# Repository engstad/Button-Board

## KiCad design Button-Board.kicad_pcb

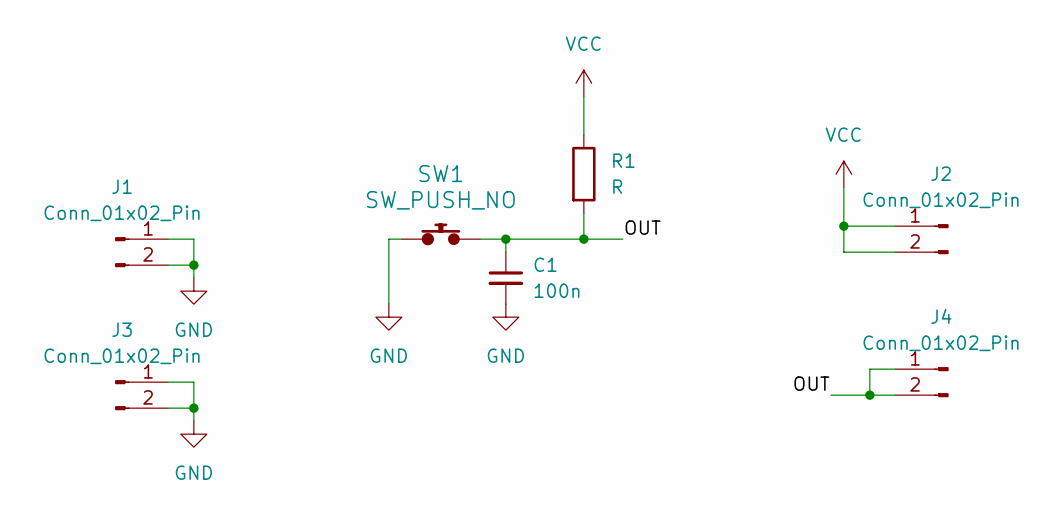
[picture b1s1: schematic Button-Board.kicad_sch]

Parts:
C1: 100n; C_0603_1608Metric_Pad1.08x0.95mm_HandSolder
J1, J2, J3, J4: Conn_01x02_Pin; PinHeader_1x02_P2.54mm_Vertical
R1: R; R_0603_1608Metric_Pad0.98x0.95mm_HandSolder
SW1: SW_PUSH_NO; TACTILE_SWITCH-TE-FSM4JSMAATR

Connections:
/OUT: C1.1, J4.1, J4.2, R1.2, SW1.2
GND: C1.2, J1.1, J1.2, J3.1, J3.2, SW1.1
VCC: J2.1, J2.2, R1.1

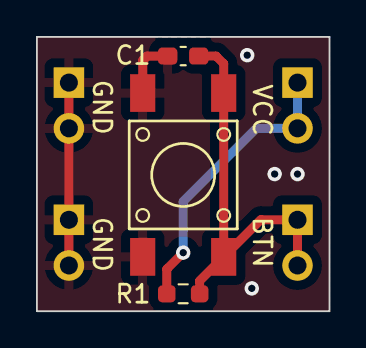
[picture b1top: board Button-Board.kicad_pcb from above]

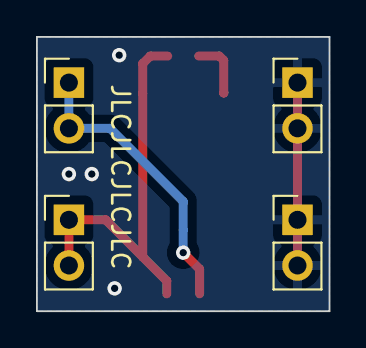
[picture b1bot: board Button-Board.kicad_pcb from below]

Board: 2 copper layers, 16.3 x 15.2 mm, 7 parts (4 on the bottom side), 3 nets.

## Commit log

2024-01-12 Initial commit.
